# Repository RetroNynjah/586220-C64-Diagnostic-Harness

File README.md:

# Retro Ninja 586220 C64 Diagnostic Harness

Eagle schematics and boards plus a combined panel of the three different boards for a C64 586220 diagnostic harmess.

This version is based on the work of [Peter Schepers](https://ist.uwaterloo.ca/~schepers/diagnostic.html) and [Sven Petersen](https://github.com/svenpetersen1965/C64-Diagnostic-Rev.-586220-Harness).
The reason I made this version was to make the boards smaller so that all three boards can fit on one PCB panel and thereby reducing the cost of the PCB by two thirds when using the 10x10cm prototype offers from PCB houses like Seeed Studio.
Making a panel also has the advantage that you can order a paste stencil with the PCB panel which makes it very easy to solder the SMD components for all three boards at once which is good if you want to build a batch of boards.

The program cartridge needed for the diagnostic program is a standard 8 Kilobyte cartridge running from $8000.
I will make schematics and gerbers for the cartridge available in a separate repository later.
ROM images for the cartridge can be found at [worldofjani.com](http://blog.worldofjani.com/?p=164).

A DIN connector loopback adapter is also required for testing the serial port. Connect pin 1 to pin 5 and connect pin 3 to pin 4.

## BOM for Cassette Port
| Component | Pcs | Name | Comment |
 |:--------|---:|:---|:------|
 | C1,C2,C3,C4 | 4 | 100nF ceramic 0805 | |
 | CN1 | 1 | 12-pin (2x6) female edge connector | 3.96mm pitch |
 | IC1,IC2,IC3 | 3 | CD4066B SOIC-14 | Quad Bilateral Switch |
 | J1,J2,J3 | 3 | 10-pin IDC male | Shrouded connector recommended |
 | LD1 | 1 | LED 3mm | Power LED |
 | R1,R2,R5,R6 | 4 | 110K 0805 | 120k works too |
 | R3,R9 | 2 | 330R 0805 | R9=current limiter for LED, 560R or even higher should be ok for R9 |
 | R8 | 1 | 10k 0805 | |
 | R4 | 1 | 150R 0805 | |
 
## BOM for User Port
 | Component | Pcs | Name | Comment |
 |:--------|---:|:---|:------|
 | C3 | 1 | 100nF ceramic 0805| |
 | LD1 | 1 | LED 3mm | Power LED |
 | R1 | 1 | 330R 0805 | Current limiter for LED. 560R or even higher should be ok |
 | SW1 | 1 | Tactile Switch 6x6mm | |
 | X1 | 1 | 24-pin (2x12) female edge connector | 3.96mm pitch |
 
## BOM for Keyboard
 | Component | Pcs | Name | Comment |
 |:--------|---:|:---|:------|
 | J1 | 1 | 20pin female header right angle|2,54mm pitch |
 | J2 | 1 | 10-pin IDC male|shrouded connector recommended |
 | LD1 | 1 | LED 1206 | Power LED |
 | R1 | 1 | 330R | Current limiter for LED. 560R or even higher should be ok |
 
## Cables
### Control port cable (2 pcs) ###
9-pin female D-SUB with IDC connection in one end and a 10-pin female IDC plug in the other end.
For each control port you need a 9 or 10 pin ribbon cable that is at least 45cm after connectors have been installed.

### Keyboard cable ###
10-pin ribbon cable with 10-pin female IDC plug on each end.

## Serial port ##
6-pin male DIN connector

Retro Ninja

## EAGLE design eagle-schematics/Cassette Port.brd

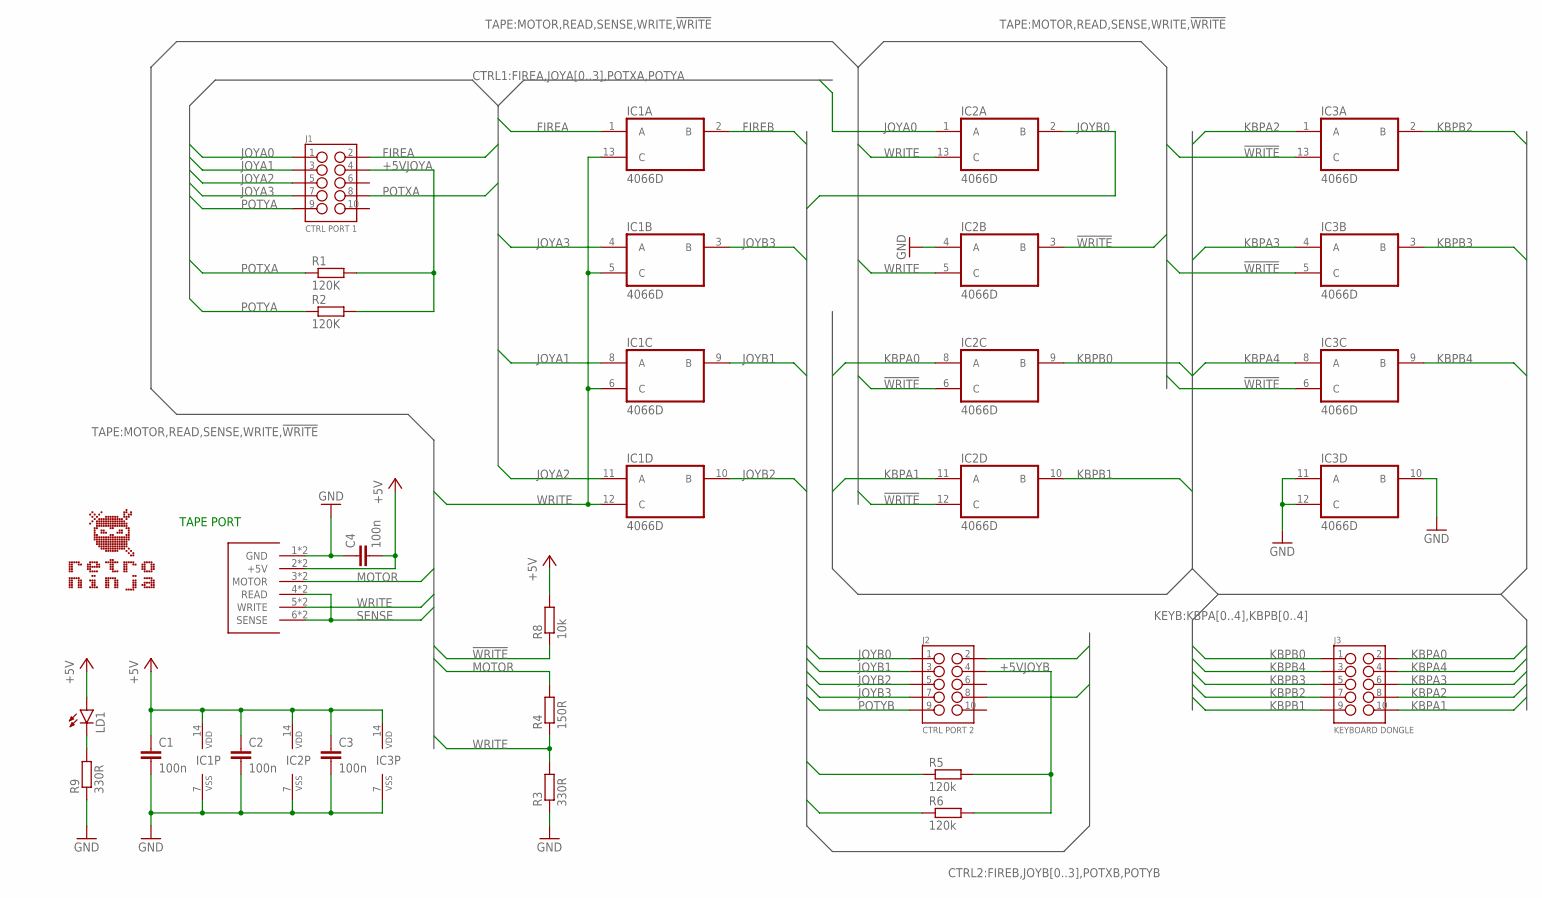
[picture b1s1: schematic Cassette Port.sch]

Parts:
C1, C2, C3, C4: 100n; C0805
CN1: C64_CASSETTE_PORT_CONNECTOR_SIDE; C64_CASSETTE_CONNECTOR
IC1, IC2, IC3: 4066D; SO14
J1: CTRL PORT 1; 2X5_HEADER_WALLED
J2: CTRL PORT 2; 2X5_HEADER_WALLED
J3: KEYBOARD DONGLE; 2X5_HEADER_WALLED
LD1: LED3MM
R1, R2: 120K; R0805
R3, R9: 330R; R0805
R4: 150R; R0805
R5, R6: 120k; R0805
R8: 10k; R0805
U$1: RETRONINJA_TEXT; RETRONINJA_TEXT_17MM

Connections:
!WRITE: IC2.3 (B), IC2.6 (C), IC2.12 (C), IC3.5 (C), IC3.6 (C), IC3.13 (C), R8.1
+5V: C1.1, C2.1, C3.1, C4.2, CN1.2 (+5V), CN1.B (+5V), IC1.14 (VDD), IC2.14 (VDD), IC3.14 (VDD), LD1.A, R8.2
+5VJOYA: J1.4, R1.2, R2.2
+5VJOYB: J2.4, R5.2, R6.2
FIREA: IC1.1 (A), J1.2
FIREB: IC1.2 (B), J2.2
GND: C1.2, C2.2, C3.2, C4.1, CN1.1 (GND), CN1.A (GND), IC1.7 (VSS), IC2.4 (A), IC2.7 (VSS), IC3.7 (VSS), IC3.10 (B), IC3.11 (A), IC3.12 (C), R3.1, R9.1
JOYA0: IC2.1 (A), J1.1
JOYA1: IC1.8 (A), J1.3
JOYA2: IC1.11 (A), J1.5
JOYA3: IC1.4 (A), J1.7
JOYB0: IC2.2 (B), J2.1
JOYB1: IC1.9 (B), J2.3
JOYB2: IC1.10 (B), J2.5
JOYB3: IC1.3 (B), J2.7
KBPA0: IC2.8 (A), J3.2
KBPA1: IC2.11 (A), J3.10
KBPA2: IC3.1 (A), J3.8
KBPA3: IC3.4 (A), J3.6
KBPA4: IC3.8 (A), J3.4
KBPB0: IC2.9 (B), J3.1
KBPB1: IC2.10 (B), J3.9
KBPB2: IC3.2 (B), J3.7
KBPB3: IC3.3 (B), J3.5
KBPB4: IC3.9 (B), J3.3
MOTOR: CN1.3 (MOTOR), CN1.C (MOTOR), R4.2
unnamed: LD1.K (C), R9.2
POTXA: J1.8, R1.1
POTXB: J2.8, R5.1
POTYA: J1.9, R2.1
POTYB: J2.9, R6.1
SENSE: CN1.4 (READ), CN1.6 (SENSE), CN1.D (READ), CN1.F (SENSE)
WRITE: CN1.5 (WRITE), CN1.E (WRITE), IC1.5 (C), IC1.6 (C), IC1.12 (C), IC1.13 (C), IC2.5 (C), IC2.13 (C), R3.2, R4.1

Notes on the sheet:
TAPE PORT

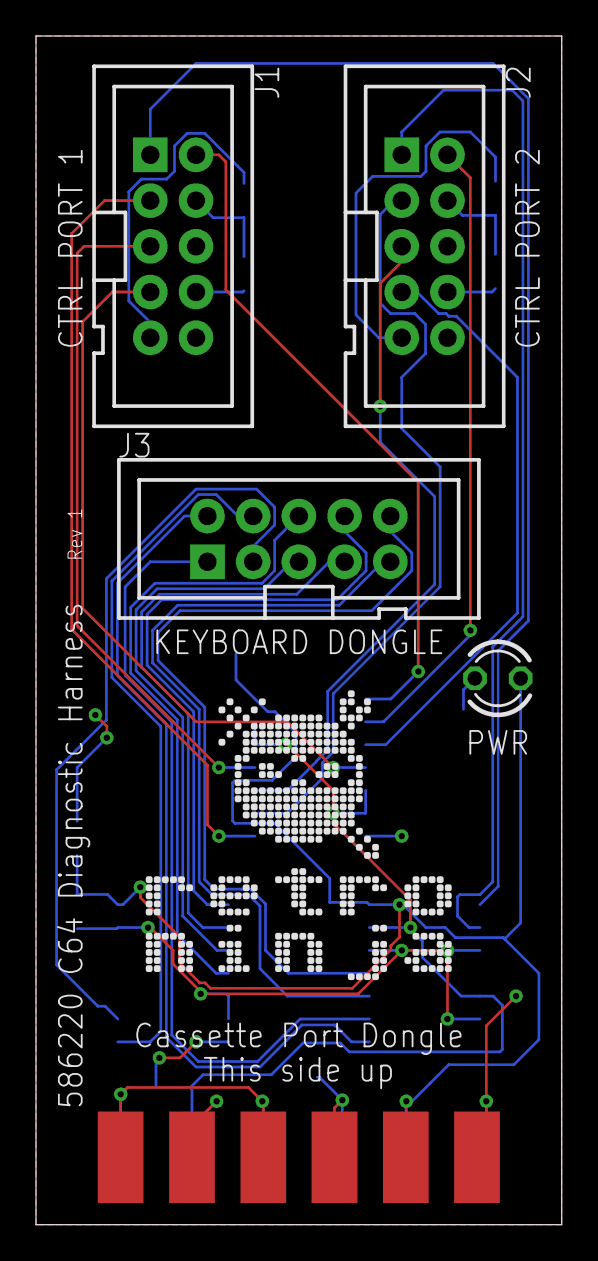
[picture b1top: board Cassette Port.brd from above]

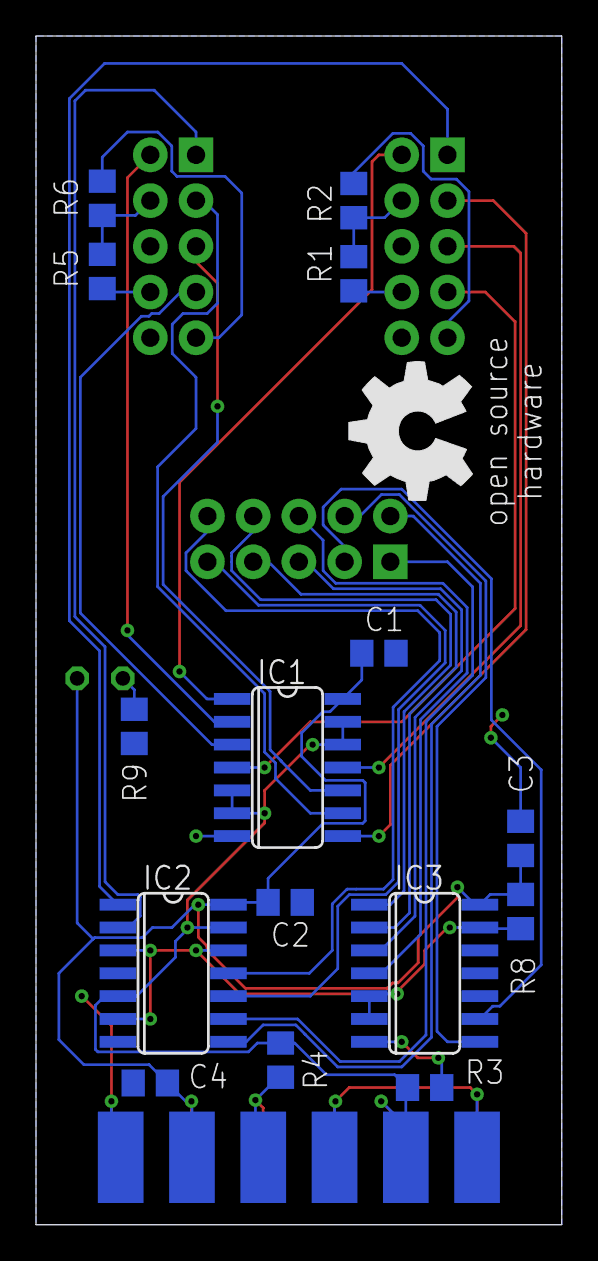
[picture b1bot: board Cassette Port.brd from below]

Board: 2 copper layers, 29.2 x 66.0 mm, 22 parts (16 on the bottom side), 33 nets.

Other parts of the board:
U$2: OSHW_8MM

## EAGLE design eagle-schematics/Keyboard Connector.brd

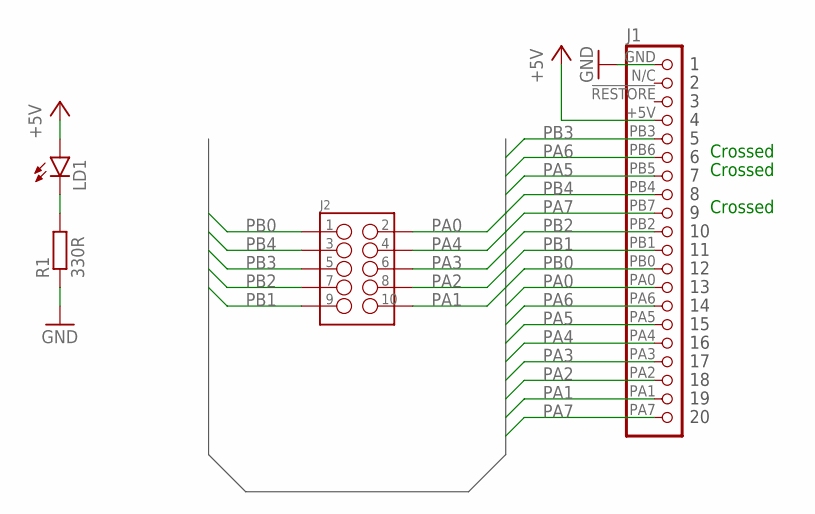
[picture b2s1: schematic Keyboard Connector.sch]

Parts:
J1: C64_KEYBOARD_CONNECTOR
J2: HEADER_2X5-WALLED; 2X5_HEADER_WALLED
LD1: LED1206; LED-1206
R1: 330R; R0805

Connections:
+5V: J1.+5V, LD1.A
GND: J1.GND, R1.1
unnamed: LD1.C, R1.2
PA0: J1.PA0, J2.2
PA1: J1.PA1, J2.10
PA2: J1.PA2, J2.8
PA3: J1.PA3, J2.6
PA4: J1.PA4, J2.4
PA5: J1.PA5, J1.PB5
PA6: J1.PA6, J1.PB6
PA7: J1.PA7, J1.PB7
PB0: J1.PB0, J2.1
PB1: J1.PB1, J2.9
PB2: J1.PB2, J2.7
PB3: J1.PB3, J2.5
PB4: J1.PB4, J2.3

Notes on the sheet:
Crossed

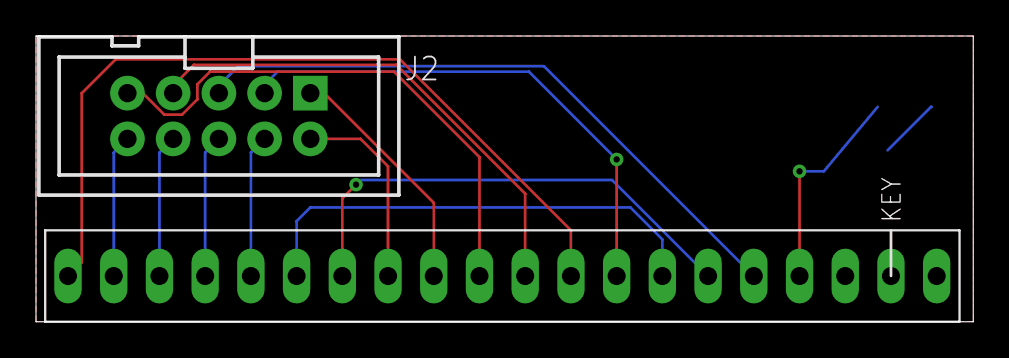
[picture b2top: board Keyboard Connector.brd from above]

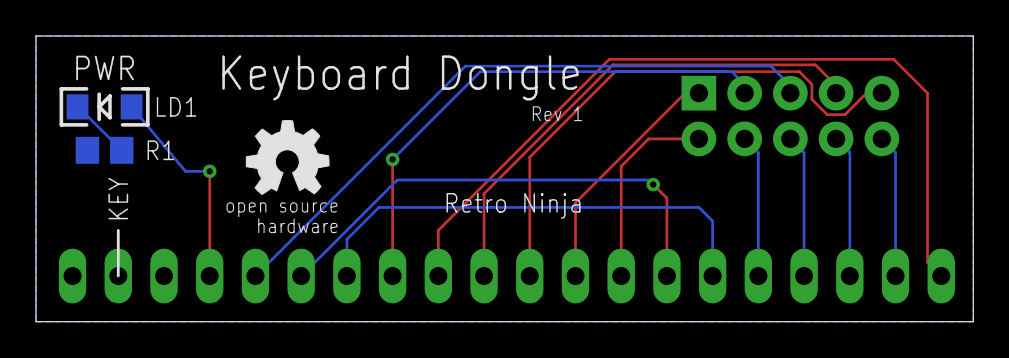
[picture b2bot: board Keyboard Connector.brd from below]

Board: 2 copper layers, 52.1 x 15.9 mm, 5 parts (3 on the bottom side), 16 nets.

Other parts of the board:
U$1: OSHW_5MM

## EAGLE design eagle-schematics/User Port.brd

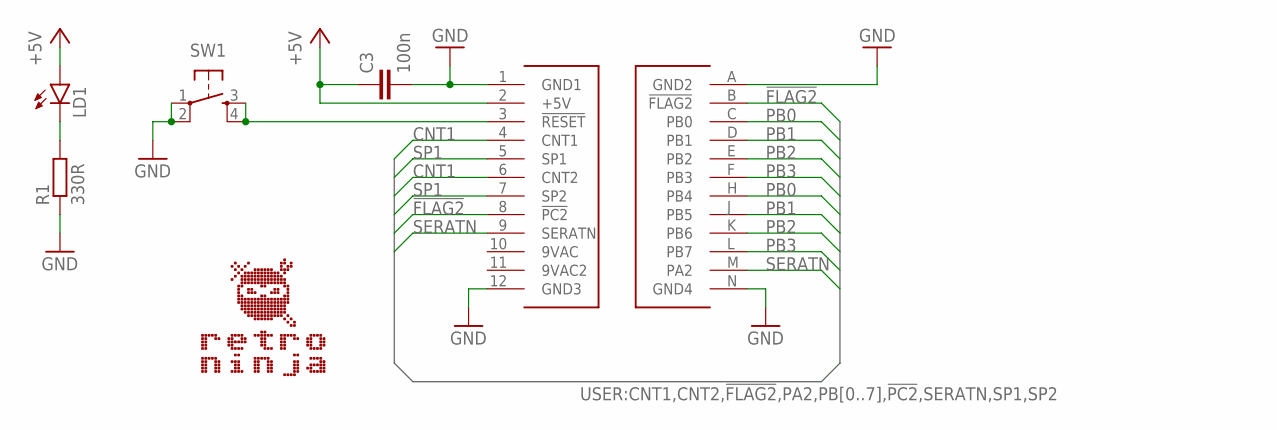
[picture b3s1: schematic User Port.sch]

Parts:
C3: 100n; C0805
LD1: LED3MM
R1: 330R; R0805
SW1: TAC_SWITCHPTH; TACTILE-PTH
U$1: RETRONINJA_TEXT; RETRONINJA_TEXT_17MM
X1: C64_USER_PORT_CONNECTOR_SIDE; C64_USER_PORT_DEVICE_CONNECTOR

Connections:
9VAC: X1.10 (9VAC)
9VAC2: X1.11 (9VAC2)
!FLAG2: X1.8 (!PC2), X1.B (!FLAG2)
!RESET: SW1.3, SW1.4, X1.3 (!RESET)
+5V: C3.1, LD1.A, X1.2 (+5V)
CNT1: X1.4 (CNT1), X1.6 (CNT2)
GND: C3.2, R1.1, SW1.1, SW1.2, X1.1 (GND1), X1.12 (GND3), X1.A (GND2), X1.N (GND4)
unnamed: LD1.K (C), R1.2
PB0: X1.C (PB0), X1.H (PB4)
PB1: X1.D (PB1), X1.J (PB5)
PB2: X1.E (PB2), X1.K (PB6)
PB3: X1.F (PB3), X1.L (PB7)
SERATN: X1.9 (SERATN), X1.M (PA2)
SP1: X1.5 (SP1), X1.7 (SP2)

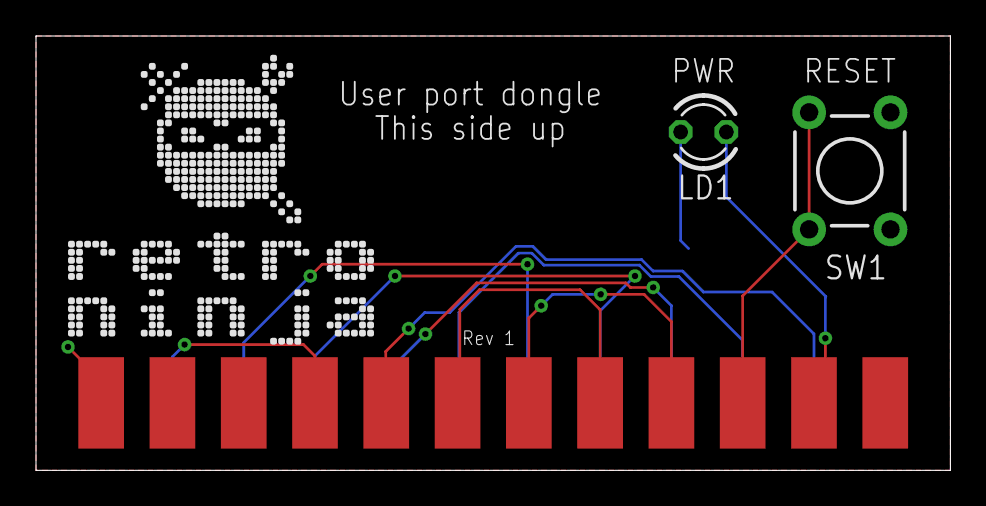
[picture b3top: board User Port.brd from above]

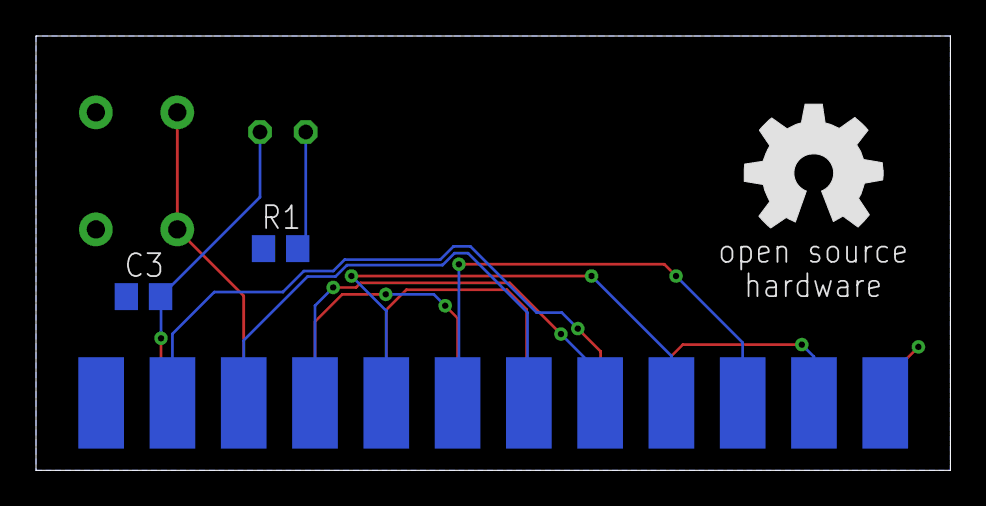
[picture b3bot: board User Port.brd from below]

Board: 2 copper layers, 50.8 x 24.1 mm, 7 parts (3 on the bottom side), 12 nets.

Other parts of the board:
U$2: OSHW_8MM

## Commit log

2020-06-01 Initial upload

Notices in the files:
parts and their libraries:
SparkFun-LED: Licensing: Creative Commons ShareAlike 4.0 International - https://creativecommons.org/licenses/by-sa/4.0
